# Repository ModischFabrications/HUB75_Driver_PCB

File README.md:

# HUB75_Driver_PCB

This is the PCB for my custom HUB75 RGB Panel Display.

I bought [this 64x32 panel](https://www.aliexpress.com/item/32810362851.html) and [this ESP32 (ESP32-CH9102X)](https://www.aliexpress.com/item/32959541446.html) closely researching specifications, costing ~30€ in sum. Others will probably work too, no guarantees either way. 

Open like regular in KiCad. Look into the docs zip under [Actions/KiCad Exports](https://github.com/ModischFabrications/HUB75_Driver_PCB/actions/workflows/exports.yml) to see renderings. 

This schematic can be soldered manually onto a perfboard, but feel free to order a PCB instead. 

Use a **5V** power supply with 10W or more! 
Never connect USB Power and Matrix power together, make sure to remove the jumper when using the USB connector. 
Powering the Matrix via USB, without the terminals, is possible, but definitely not recommended, the devboard can't handle it. 

Max current is ~2A, typical ~0.7A, idle (without output) is still ~0.06A, split between devboard and RGB controllers. 
Being wireless it nice, but usually, especially in this case, not worth the effort for protoypes. 
While technically possible, the power draw will reduce battery runtime to less than a day.  

Feel free to add external solutions though, should be easy to cram a 18650 USP board into the case. 

## Decisions

Size and exact positioning is determined by the backing struts of my panel. 

Using a 30 Pin Devboard keeps everything compact, but means that IO options are limited. Many pins of the ESP32 have limited usability or are otherwise reserved, check [pinouts](https://i0.wp.com/randomnerdtutorials.com/wp-content/uploads/2018/08/ESP32-DOIT-DEVKIT-V1-Board-Pinout-30-GPIOs-Copy.png) for reference. This board contains 2 (/3) Touch Inputs for future expansion, a full I2C/SPI/... wasn't included due to size constraints. 

### Electrical

Short-circuit-resistance of the power leads is archieved using a polyfuse. Resistance of the inputs is build-in, as they are high impedance, but the outputs are at risk. 

Reverse polarity protection is given through D1, which will trigger the fuse. Sure, it's not perfect, but it's simple. 

Introducing series resistances into every single connection could have made it safer, but I can't be arsed at the moment. Active-Low or High doesn't really matter either, a cross between adjacent leads would result in one overloading regardless. Feel free to insert ~300 ohm everywhere if you want to be safe. 

## References
To be honest, they are virtually identical solutions with just minor differences. Choose according to your needs. 

- https://github.com/rorosaurus/esp32-hub75-driver
- https://github.com/witnessmenow/ESP32-i2s-Matrix-Shield

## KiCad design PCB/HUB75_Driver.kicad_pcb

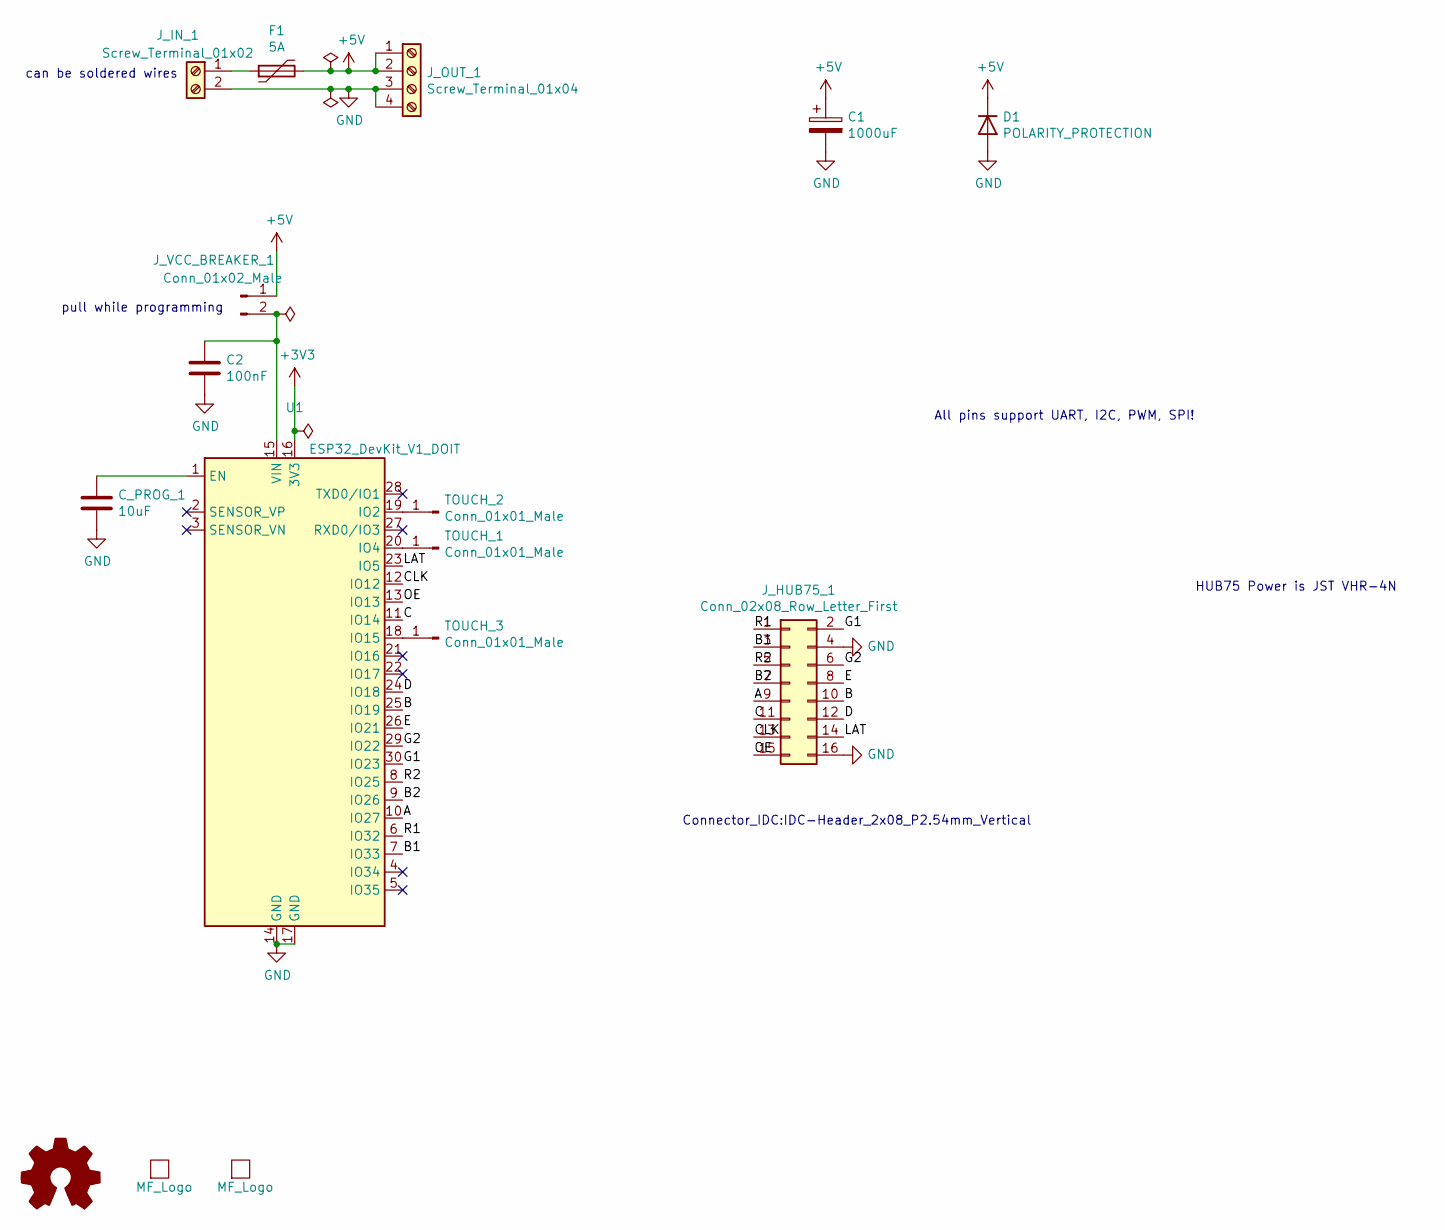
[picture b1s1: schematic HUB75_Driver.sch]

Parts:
C1: 1000uF; CP_10x20mm_hor
C2: 100nF; C_0603_1608Metric
C_PROG_1: 10uF; C_0603_1608Metric
D1: POLARITY_PROTECTION; D_DO-35_SOD27_P7.62mm_Horizontal
F1: 5A; Fuse_0805_2012Metric_Pad1.15x1.40mm_HandSolder
J_HUB75_1: Conn_02x08_Row_Letter_First; PinSocket_2x08_P2.54mm_Vertical
J_IN_1: Screw_Terminal_01x02; TerminalBlock_bornier-2_P5.08mm
J_OUT_1: Screw_Terminal_01x04; TerminalBlock_bornier-4_P5.08mm
J_VCC_BREAKER_1: Conn_01x02_Male; PinHeader_1x02_P2.54mm_Horizontal
L1, L2: MF_Logo; mf_logo_10mm
LOGO1: Logo_Open_Hardware_Small; OSHW-Logo2_7.3x6mm_SilkScreen
TOUCH_1, TOUCH_2, TOUCH_3: Conn_01x01_Male; PinHeader_1x01_P2.54mm_Horizontal
U1: ESP32_DevKit_V1_DOIT; esp32_devkit_v1_doit

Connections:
+5V: C1.1, D1.1 (K), F1.2, J_OUT_1.1, J_OUT_1.2, J_VCC_BREAKER_1.1
/A: J_HUB75_1.9, U1.10 (IO27)
/B: J_HUB75_1.10, U1.25 (IO19)
/B1: J_HUB75_1.3, U1.7 (IO33)
/B2: J_HUB75_1.7, U1.9 (IO26)
/C: J_HUB75_1.11, U1.11 (IO14)
/CLK: J_HUB75_1.13, U1.12 (IO12)
/D: J_HUB75_1.12, U1.24 (IO18)
/E: J_HUB75_1.8, U1.26 (IO21)
/G1: J_HUB75_1.2, U1.30 (IO23)
/G2: J_HUB75_1.6, U1.29 (IO22)
/LAT: J_HUB75_1.14, U1.23 (IO5)
/OE: J_HUB75_1.15, U1.13 (IO13)
/R1: J_HUB75_1.1, U1.6 (IO32)
/R2: J_HUB75_1.5, U1.8 (IO25)
GND: C1.2, C2.2, C_PROG_1.2, D1.2 (A), J_HUB75_1.4, J_HUB75_1.16, J_IN_1.2, J_OUT_1.3, J_OUT_1.4, U1.14 (GND), U1.17 (GND)
unnamed: C2.1, J_VCC_BREAKER_1.2, U1.15 (VIN)
unnamed: C_PROG_1.1, U1.1 (EN)
unnamed: F1.1, J_IN_1.1
unnamed: TOUCH_1.1, U1.20 (IO4)
unnamed: TOUCH_2.1, U1.19 (IO2)
unnamed: TOUCH_3.1, U1.18 (IO15)

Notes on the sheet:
can be soldered wires
pull while programming
HUB75 Power is JST VHR-4N
All pins support UART, I2C, PWM, SPI!
Connector_IDC:IDC-Header_2x08_P2.54mm_Vertical

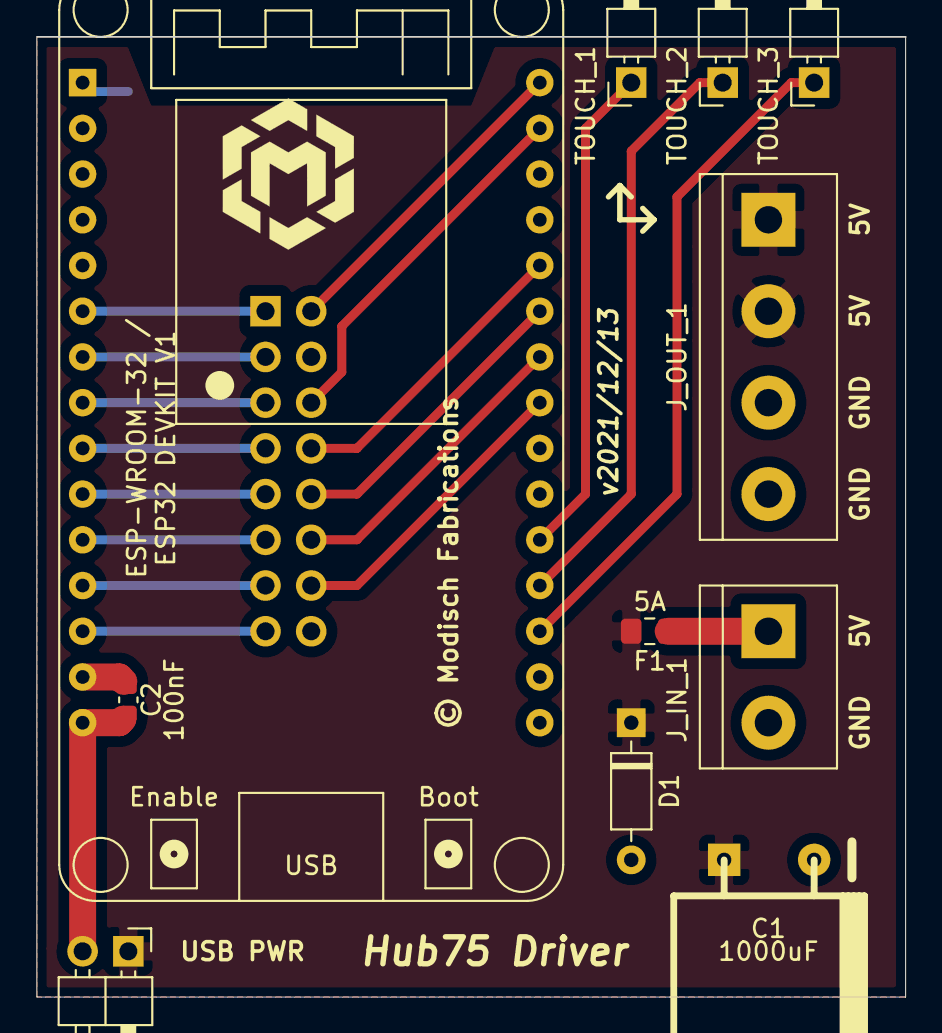
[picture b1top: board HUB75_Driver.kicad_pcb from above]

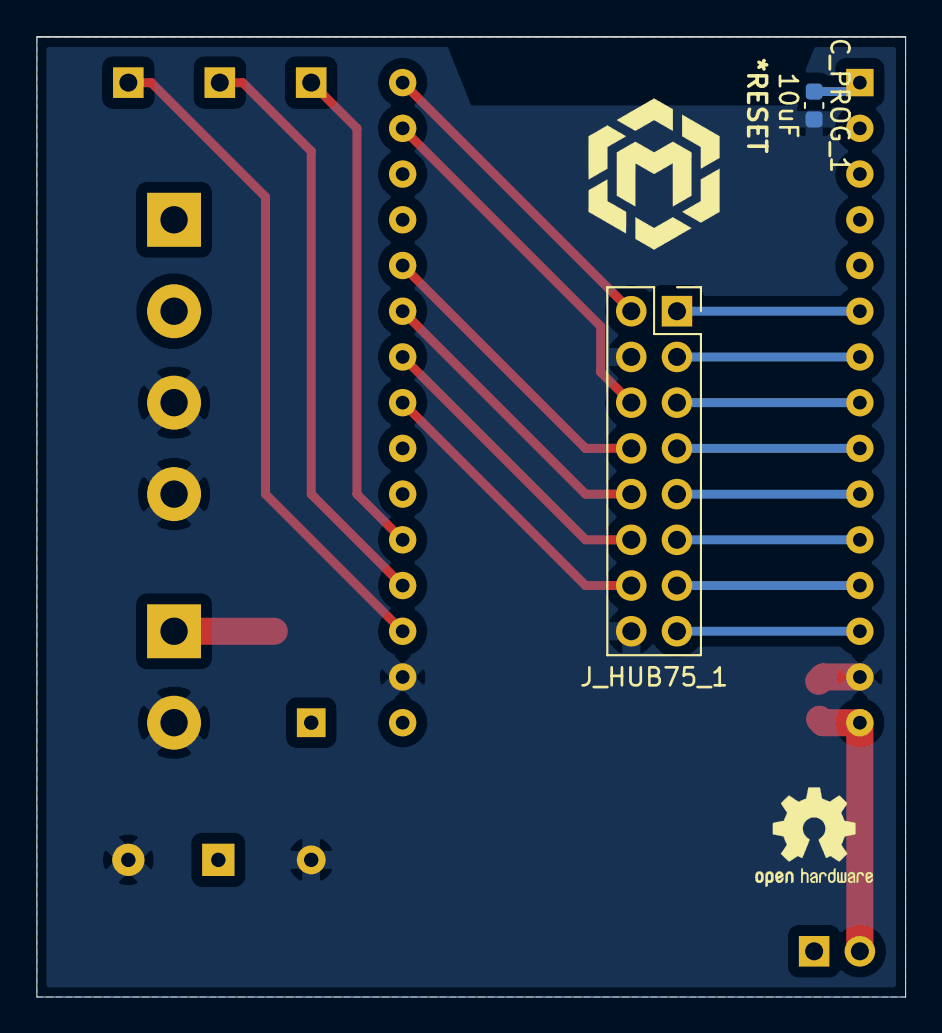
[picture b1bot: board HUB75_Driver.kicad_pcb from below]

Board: 2 copper layers, 48.3 x 53.3 mm, 16 parts (4 on the bottom side), 22 nets.

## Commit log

2021-12-13 init
2021-12-13 fix missing wires, use blue PCB
2021-12-14 refine CI/CD
2021-12-14 add reset capacitor
2023-01-16 Create LICENSE

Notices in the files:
PCB/HUB75_Driver.kicad_pcb:
© Modisch Fabrications
